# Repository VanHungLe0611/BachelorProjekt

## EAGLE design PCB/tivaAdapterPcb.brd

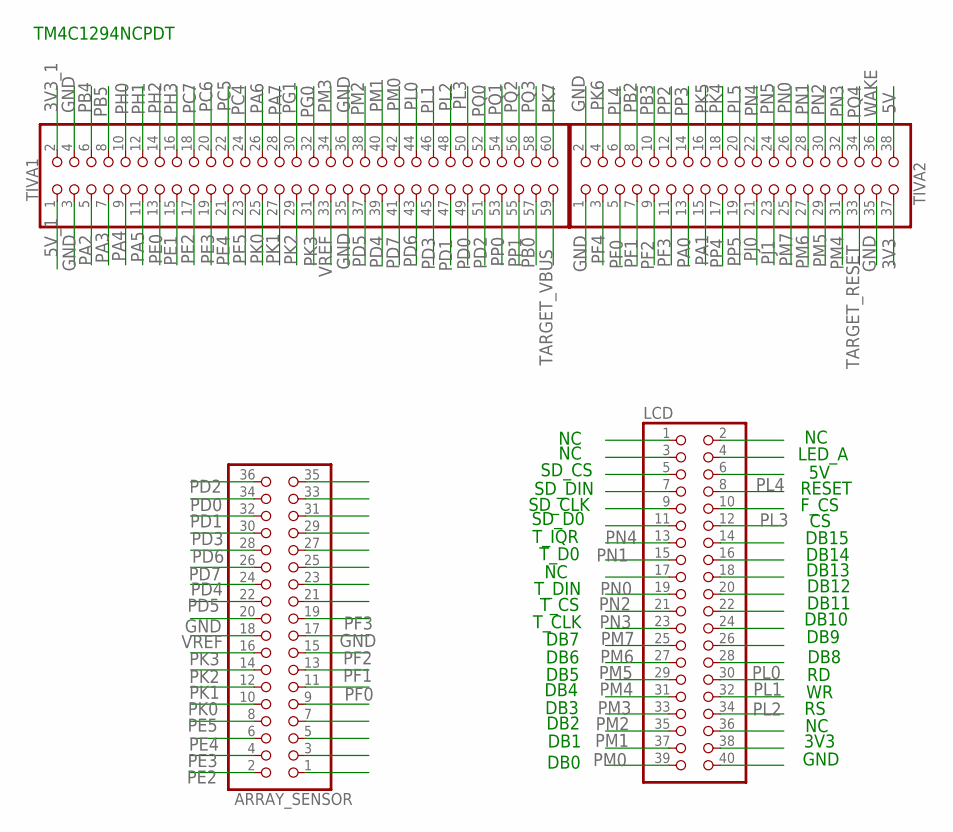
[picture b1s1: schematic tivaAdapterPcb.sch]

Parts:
ARRAY_SENSOR: PINHD-2X18; 2X18
LCD: PINHD-2X20; 2X20
TIVA1: PINHD-2X30; 2X30
TIVA2: PINHD-2X19; 2X19

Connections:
3V3: TIVA2.37
3V3_1: TIVA1.2
5V: TIVA2.38
5V_1: TIVA1.1
GND: ARRAY_SENSOR.17, ARRAY_SENSOR.20, TIVA1.3, TIVA1.4, TIVA1.35, TIVA1.36, TIVA2.1, TIVA2.2, TIVA2.35
PA0: TIVA2.13
PA1: TIVA2.15
PA2: TIVA1.5
PA3: TIVA1.7
PA4: TIVA1.9
PA5: TIVA1.11
PA6: TIVA1.26
PA7: TIVA1.28
PB0: TIVA1.57
PB2: TIVA2.8
PB3: TIVA2.10
PB4: TIVA1.6
PB5: TIVA1.8
PC4: TIVA1.24
PC5: TIVA1.22
PC6: TIVA1.20
PC7: TIVA1.18
PD0: ARRAY_SENSOR.34, TIVA1.49
PD1: ARRAY_SENSOR.32, TIVA1.47
PD2: ARRAY_SENSOR.36, TIVA1.51
PD3: ARRAY_SENSOR.30, TIVA1.45
PD4: ARRAY_SENSOR.24, TIVA1.39
PD5: ARRAY_SENSOR.22, TIVA1.37
PD6: ARRAY_SENSOR.28, TIVA1.43
PD7: ARRAY_SENSOR.26, TIVA1.41
PE0: TIVA1.13
PE1: TIVA1.15
PE2: ARRAY_SENSOR.2, TIVA1.17
PE3: ARRAY_SENSOR.4, TIVA1.19
PE4: ARRAY_SENSOR.6, TIVA1.21
PE5: ARRAY_SENSOR.8, TIVA1.23
PF0: ARRAY_SENSOR.11, TIVA2.5
PF1: ARRAY_SENSOR.13, TIVA2.7
PF2: ARRAY_SENSOR.15, TIVA2.9
PF3: ARRAY_SENSOR.19, TIVA2.11
PF4: TIVA2.3
PG0: TIVA1.32
PG1: TIVA1.30
PH0: TIVA1.10
PH1: TIVA1.12
PH2: TIVA1.14
PH3: TIVA1.16
PJ0: TIVA2.21
PJ1: TIVA2.23
PK0: ARRAY_SENSOR.10, TIVA1.25
PK1: ARRAY_SENSOR.12, TIVA1.27
PK2: ARRAY_SENSOR.14, TIVA1.29
PK3: ARRAY_SENSOR.16, TIVA1.31
PK4: TIVA2.18
PK5: TIVA2.16
PK6: TIVA2.4
PK7: TIVA1.60
PL0: LCD.30, TIVA1.44
PL1: LCD.32, TIVA1.46
PL2: LCD.34, TIVA1.48
PL3: LCD.12, TIVA1.50
PL4: LCD.8, TIVA2.6
PL5: TIVA2.20
PM0: LCD.39, TIVA1.42
PM1: LCD.37, TIVA1.40
PM2: LCD.35, TIVA1.38
PM3: LCD.33, TIVA1.34
PM4: LCD.31, TIVA2.31
PM5: LCD.29, TIVA2.29
PM6: LCD.27, TIVA2.27
PM7: LCD.25, TIVA2.25
PN0: LCD.19, TIVA2.26
PN1: LCD.15, TIVA2.28
PN2: LCD.21, TIVA2.30
PN3: LCD.23, TIVA2.32
PN4: LCD.13, TIVA2.22
PN5: TIVA2.24
PP0: TIVA1.53
PP1: TIVA1.55
PP2: TIVA2.12
PP3: TIVA2.14
PP4: TIVA2.17
PP5: TIVA2.19
PQ0: TIVA1.52
PQ1: TIVA1.54
PQ2: TIVA1.56
PQ3: TIVA1.58
PQ4: TIVA2.34
TARGET_RESET: TIVA2.33
TARGET_VBUS: TIVA1.59
VREF: ARRAY_SENSOR.18, TIVA1.33
WAKE: TIVA2.36

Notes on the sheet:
TM4C1294NCPDT
LED_A
RESET
F_CS
DB15
DB14
DB13
DB12
DB11
DB10
DB9
DB8
3V3
GND
SD_CS
SD_DIN
SD_CLK
SD_D0
T_IQR
T_D0
T_DIN
T_CS
T_CLK
DB7
DB6
DB5
DB4
DB3
DB2
DB1
DB0

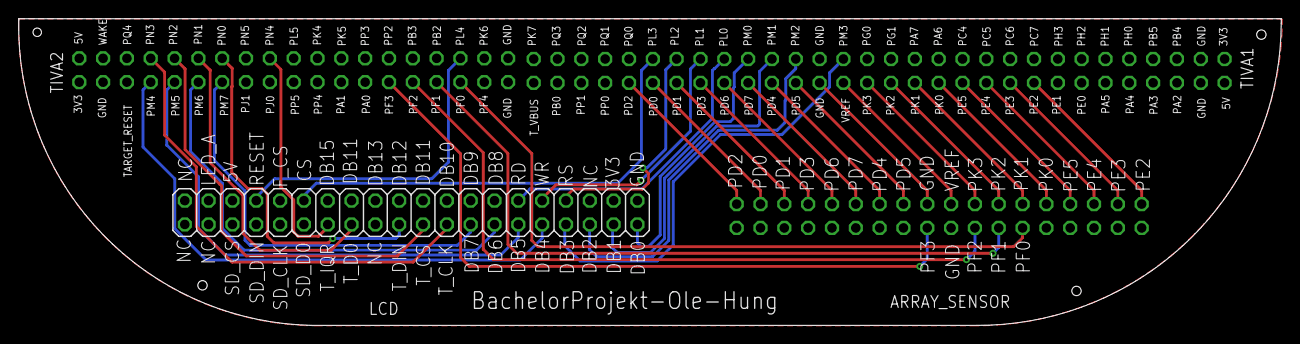
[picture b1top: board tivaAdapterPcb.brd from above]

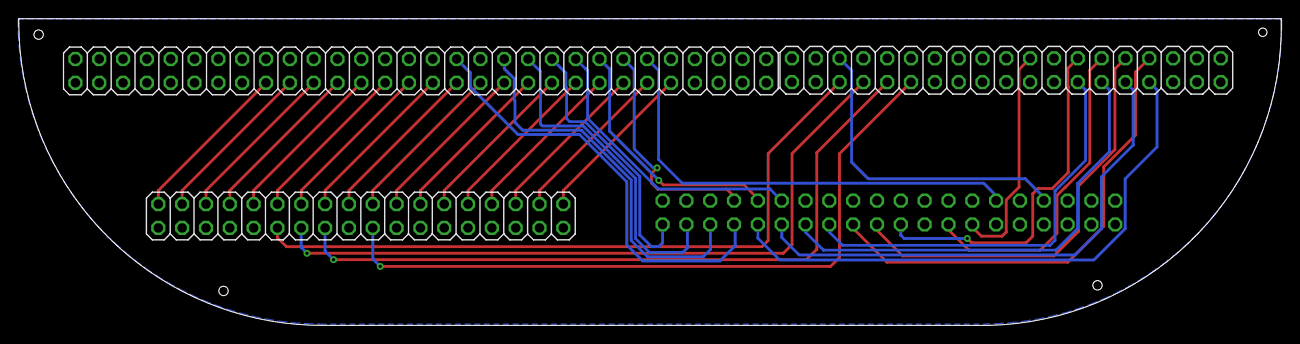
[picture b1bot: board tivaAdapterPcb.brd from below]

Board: 2 copper layers, 134.6 x 32.7 mm, 4 parts (3 on the bottom side), 40 nets.

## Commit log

2020-02-17 design lcd and array_sensor with tiva c serie
2020-02-17 route
2020-02-18 add pin name
